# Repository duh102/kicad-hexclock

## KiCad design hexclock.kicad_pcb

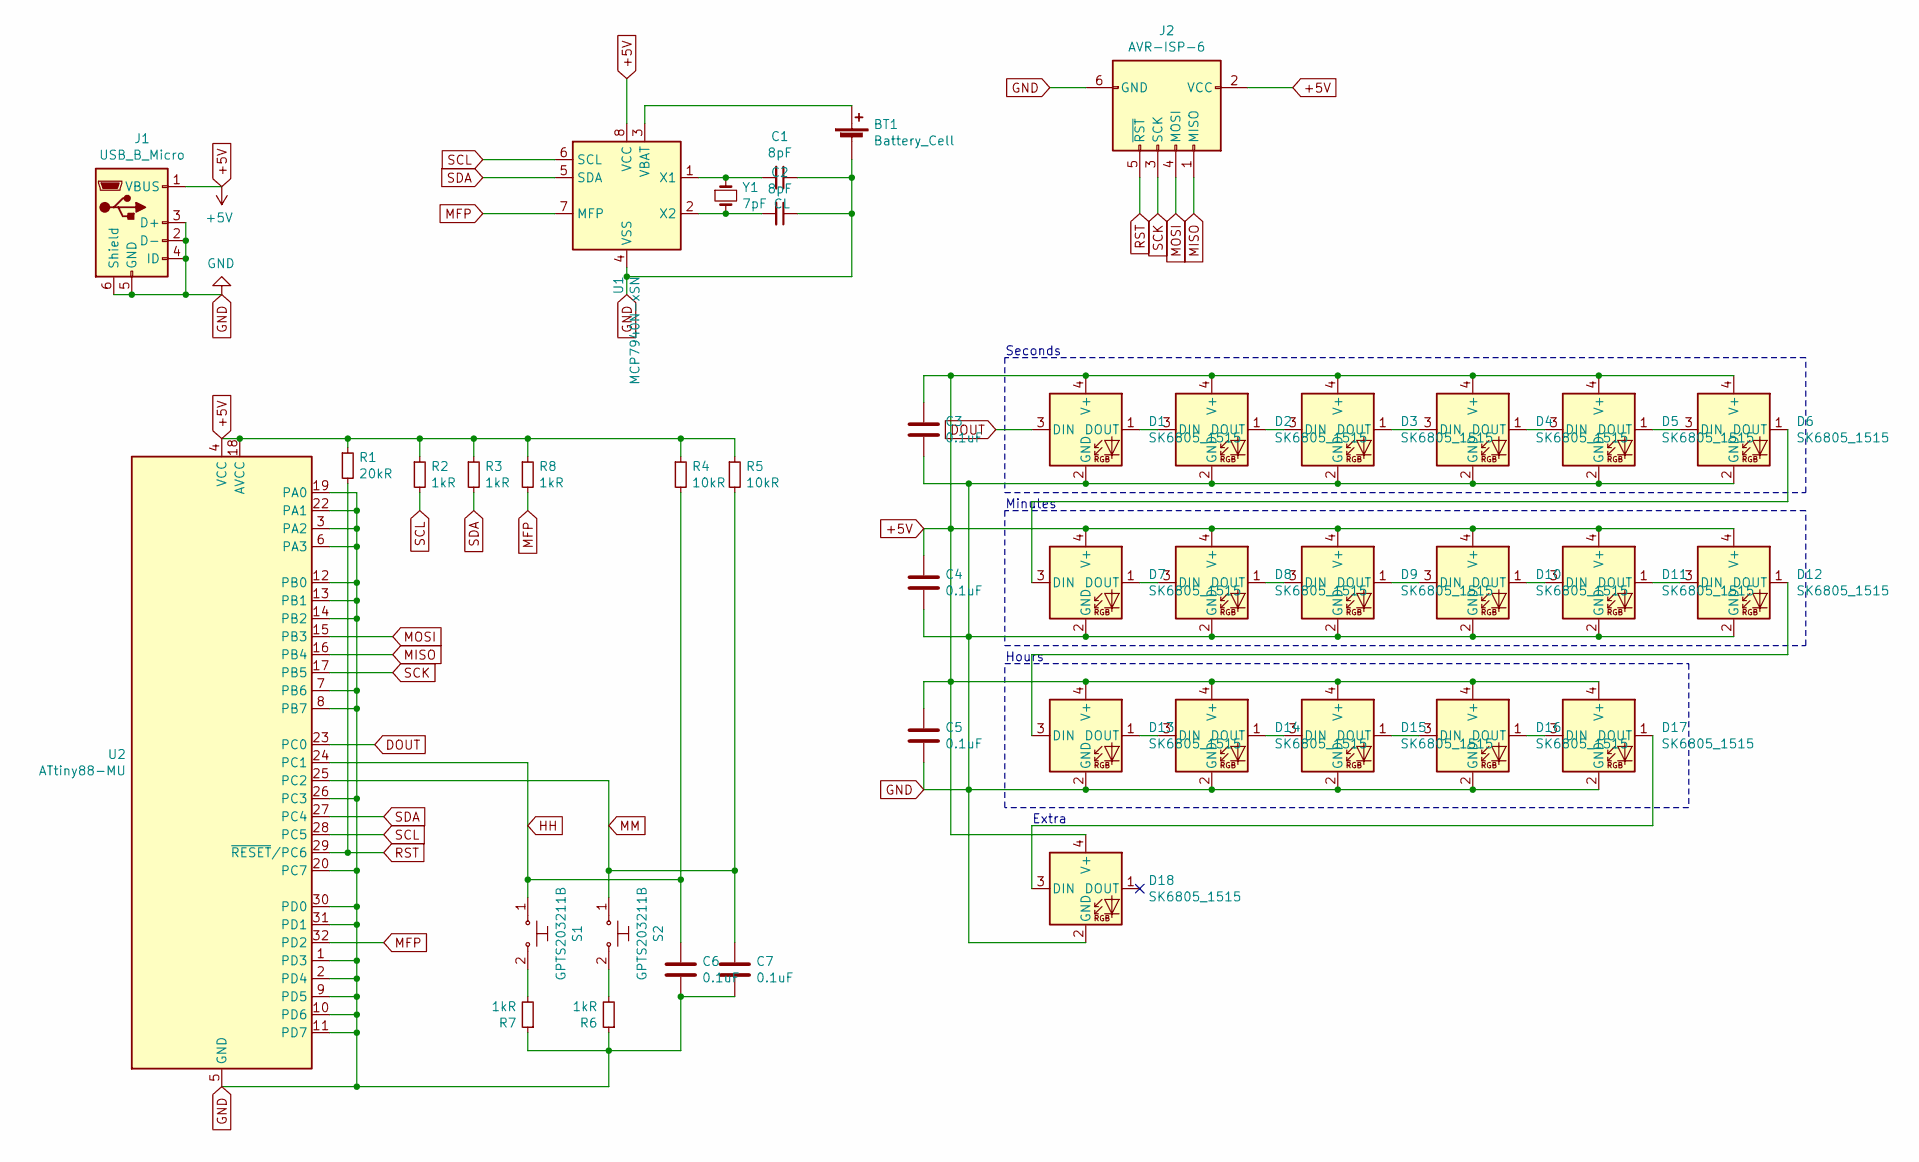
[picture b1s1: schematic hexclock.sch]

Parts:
BT1: Battery_Cell; BatteryHolder_Keystone_3034_1x20mm
C1, C2: 8pF; C_0805_2012Metric
C3, C4, C5, C6, C7: 0.1uF; C_0805_2012Metric
D1, D2, D3, D4, D5, D6, D7, D8, D9, D10, D11, D12, D13, D14, D15, D16, D17, D18: SK6805_1515; LED_SK6805_PLCC4_1.5x1.5mm_P0.65mm
J1: USB_B_Micro; USB_Micro_B_Female_10118194-0001LF
J2: AVR-ISP-6; PinHeader_2x03_P2.54mm_Vertical_SMD
R1: 20kR; R_0805_2012Metric
R2, R3, R6, R7, R8: 1kR; R_0805_2012Metric
R4, R5: 10kR; R_0805_2012Metric
S1, S2: GPTS203211B; SW_SPST_FSMSM; MPN GPTS203211B; Digi-Key_PN CW181-ND
U1: MCP7940N-xSN; SOIC-8_3.9x4.9mm_P1.27mm
U2: ATtiny88-MU; TQFP-32_7x7mm_P0.8mm
Y1: 7pF CL; Crystal_SMD_3215-2Pin_3.2x1.5mm

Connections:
+5V: C3.1, C4.1, C5.1, D1.4 (V+), D2.4 (V+), D3.4 (V+), D4.4 (V+), D5.4 (V+), D6.4 (V+), D7.4 (V+), D8.4 (V+), D9.4 (V+), D10.4 (V+), D11.4 (V+), D12.4 (V+), D13.4 (V+), D14.4 (V+), D15.4 (V+), D16.4 (V+), D17.4 (V+), D18.4 (V+), J1.1 (VBUS), J2.2 (VCC), R1.1, R2.1, R3.1, R4.1, R5.1, R8.1, U1.8 (VCC), U2.4 (VCC), U2.18 (AVCC)
DOUT: D1.3 (DIN), U2.23 (PC0)
GND: BT1.2 (-), C1.1, C2.1, C3.2, C4.2, C5.2, C6.2, C7.2, D1.2 (GND), D2.2 (GND), D3.2 (GND), D4.2 (GND), D5.2 (GND), D6.2 (GND), D7.2 (GND), D8.2 (GND), D9.2 (GND), D10.2 (GND), D11.2 (GND), D12.2 (GND), D13.2 (GND), D14.2 (GND), D15.2 (GND), D16.2 (GND), D17.2 (GND), D18.2 (GND), J1.2 (D-), J1.3 (D+), J1.4 (ID), J1.5 (GND), J1.6 (Shield), J2.6 (GND), R6.1, R7.1, U1.4 (VSS), U2.1 (PD3), U2.2 (PD4), U2.3 (PA2), U2.5 (GND), U2.6 (PA3), U2.7 (PB6), U2.8 (PB7), U2.9 (PD5), U2.10 (PD6), U2.11 (PD7), U2.12 (PB0), U2.13 (PB1), U2.14 (PB2), U2.19 (PA0), U2.20 (PC7), U2.21 (GND), U2.22 (PA1), U2.26 (PC3), U2.30 (PD0), U2.31 (PD1)
HH: C6.1, R4.2, S1.1, U2.24 (PC1)
MFP: R8.2, U1.7 (MFP), U2.32 (PD2)
MISO: J2.1 (MISO), U2.16 (PB4)
MM: C7.1, R5.2, S2.1, U2.25 (PC2)
MOSI: J2.4 (MOSI), U2.15 (PB3)
unnamed: BT1.1 (+), U1.3 (VBAT)
unnamed: C1.2, U1.1 (X1), Y1.1
unnamed: C2.2, U1.2 (X2), Y1.2
unnamed: D1.1 (DOUT), D2.3 (DIN)
unnamed: D2.1 (DOUT), D3.3 (DIN)
unnamed: D3.1 (DOUT), D4.3 (DIN)
unnamed: D4.1 (DOUT), D5.3 (DIN)
unnamed: D5.1 (DOUT), D6.3 (DIN)
unnamed: D6.1 (DOUT), D7.3 (DIN)
unnamed: D7.1 (DOUT), D8.3 (DIN)
unnamed: D8.1 (DOUT), D9.3 (DIN)
unnamed: D10.1 (DOUT), D11.3 (DIN)
unnamed: D9.1 (DOUT), D10.3 (DIN)
unnamed: D11.1 (DOUT), D12.3 (DIN)
unnamed: D12.1 (DOUT), D13.3 (DIN)
unnamed: D13.1 (DOUT), D14.3 (DIN)
unnamed: D14.1 (DOUT), D15.3 (DIN)
unnamed: D15.1 (DOUT), D16.3 (DIN)
unnamed: D16.1 (DOUT), D17.3 (DIN)
unnamed: D17.1 (DOUT), D18.3 (DIN)
unnamed: R6.2, S2.2
unnamed: R7.2, S1.2
RST: J2.5 (~RST), R1.2, U2.29 (~RESET~/PC6)
SCK: J2.3 (SCK), U2.17 (PB5)
SCL: R2.2, U1.6 (SCL), U2.28 (PC5)
SDA: R3.2, U1.5 (SDA), U2.27 (PC4)

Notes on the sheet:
Seconds
Minutes
Hours
Extra

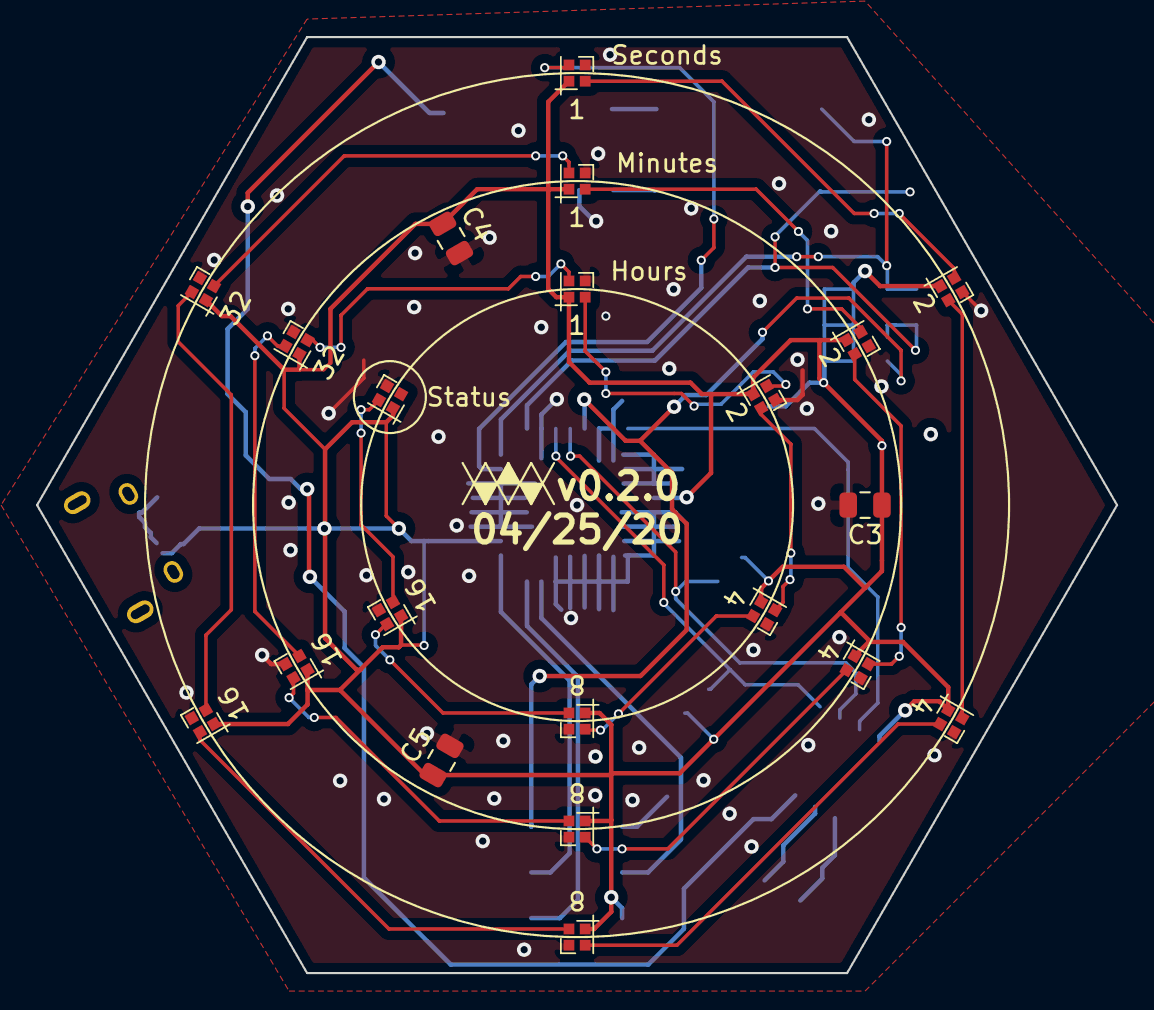
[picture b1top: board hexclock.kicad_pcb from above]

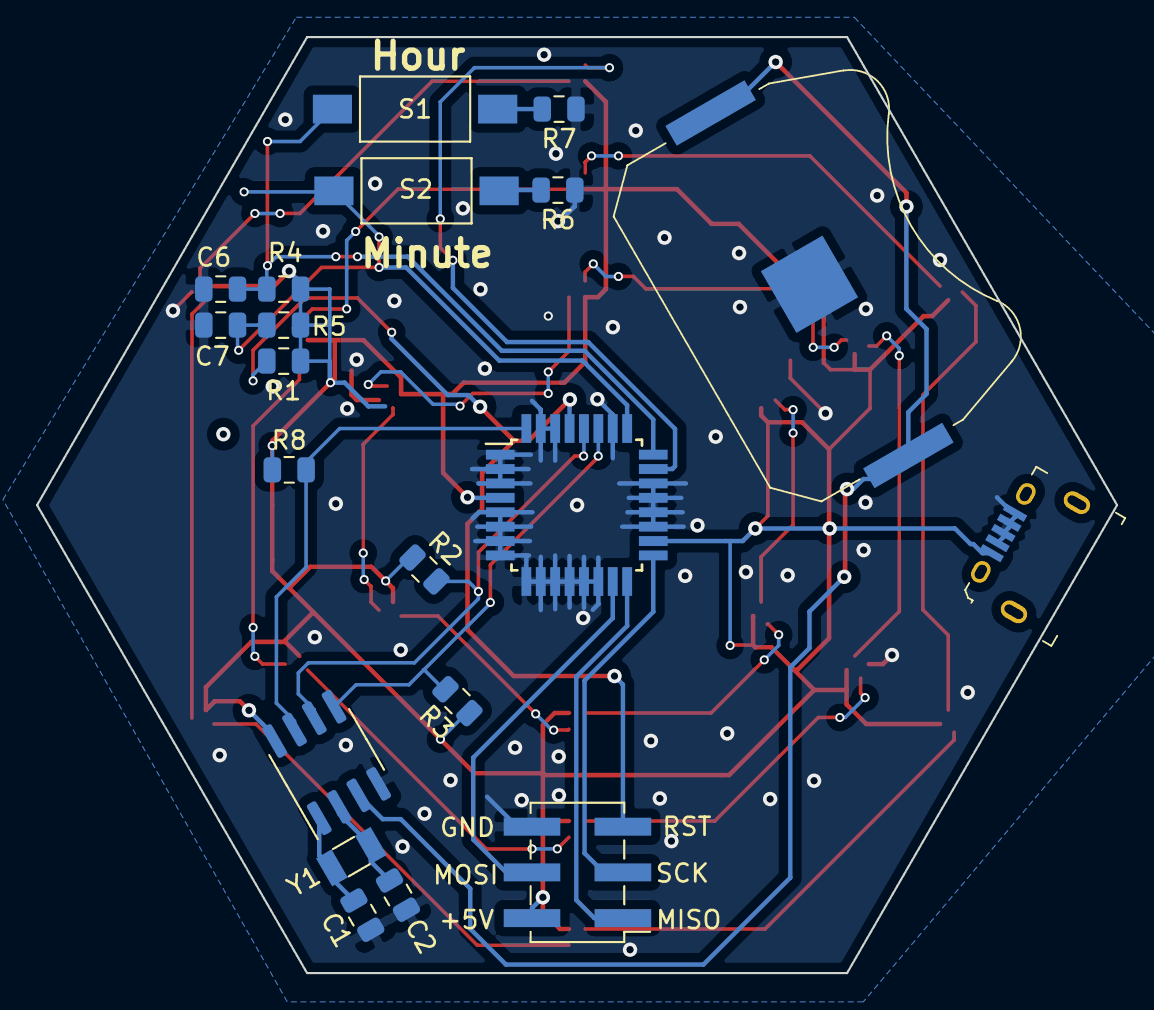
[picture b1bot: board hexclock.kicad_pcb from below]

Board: 2 copper layers, 60.0 x 52.0 mm, 41 parts (20 on the bottom side), 34 nets.

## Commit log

2020-04-03 Schematic for hexclock
2020-04-04 v0.0.0 finished
2020-04-05 Fix i2c pullups
2020-04-15 Switch to using oscillator; update version
2020-04-16 Optimize ground plane + vias
2020-04-25 Change time mech to RTC
